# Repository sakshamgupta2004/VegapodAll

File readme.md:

1. This is the all the vegapod work from my side
2. MP4s are not uploaded for obvious reasons
3. some backup folders generated by kicad and other cache is added to gitignore aswell
4. If any folder appears empty when it should have content, its probably added to gitignore
5. Contains Videos, Images, PCB designs, Meeting info, Documents such as fdd and itd, SPICE simulations, etc

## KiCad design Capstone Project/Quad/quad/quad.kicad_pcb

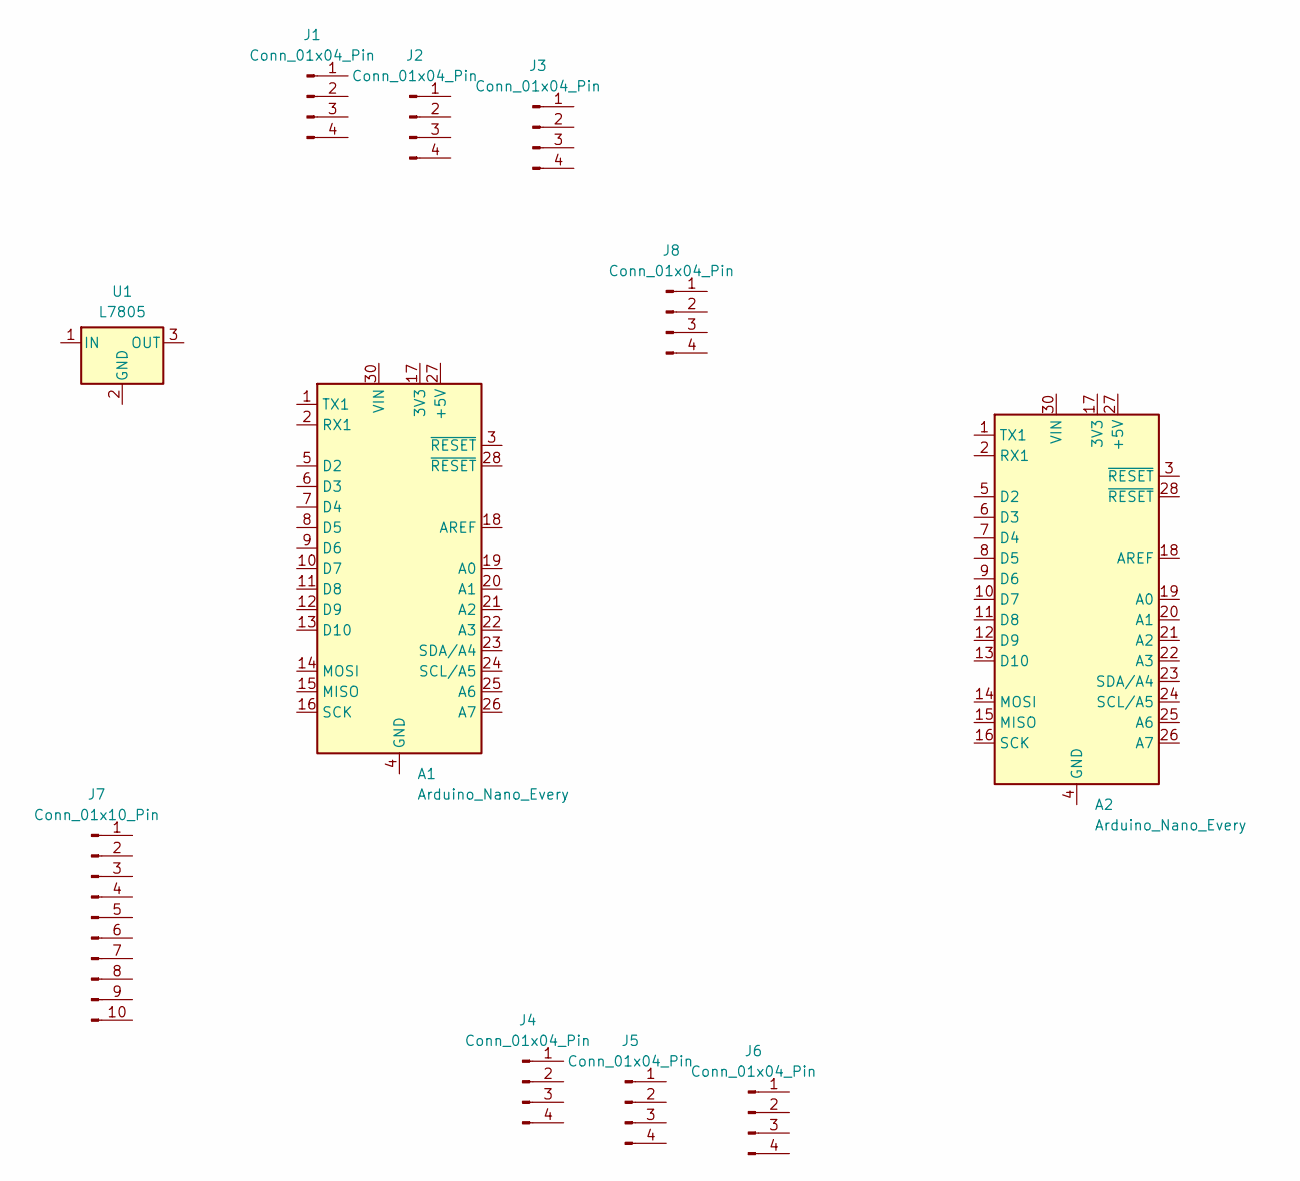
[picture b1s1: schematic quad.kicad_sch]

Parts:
A1, A2: Arduino_Nano_Every; Arduino_Nano
J1, J2, J3, J4, J5, J6, J8: Conn_01x04_Pin; PinHeader_1x04_P2.54mm_Vertical
J7: Conn_01x10_Pin; PinHeader_1x10_P2.54mm_Vertical
U1: L7805; TO-220-3_Vertical

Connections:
unnamed: A1.4 (GND), A1.29 (GND)
unnamed: A2.4 (GND), A2.29 (GND)

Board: 2 copper layers, 11 parts (0 on the bottom side), 2 nets, no tracks yet.

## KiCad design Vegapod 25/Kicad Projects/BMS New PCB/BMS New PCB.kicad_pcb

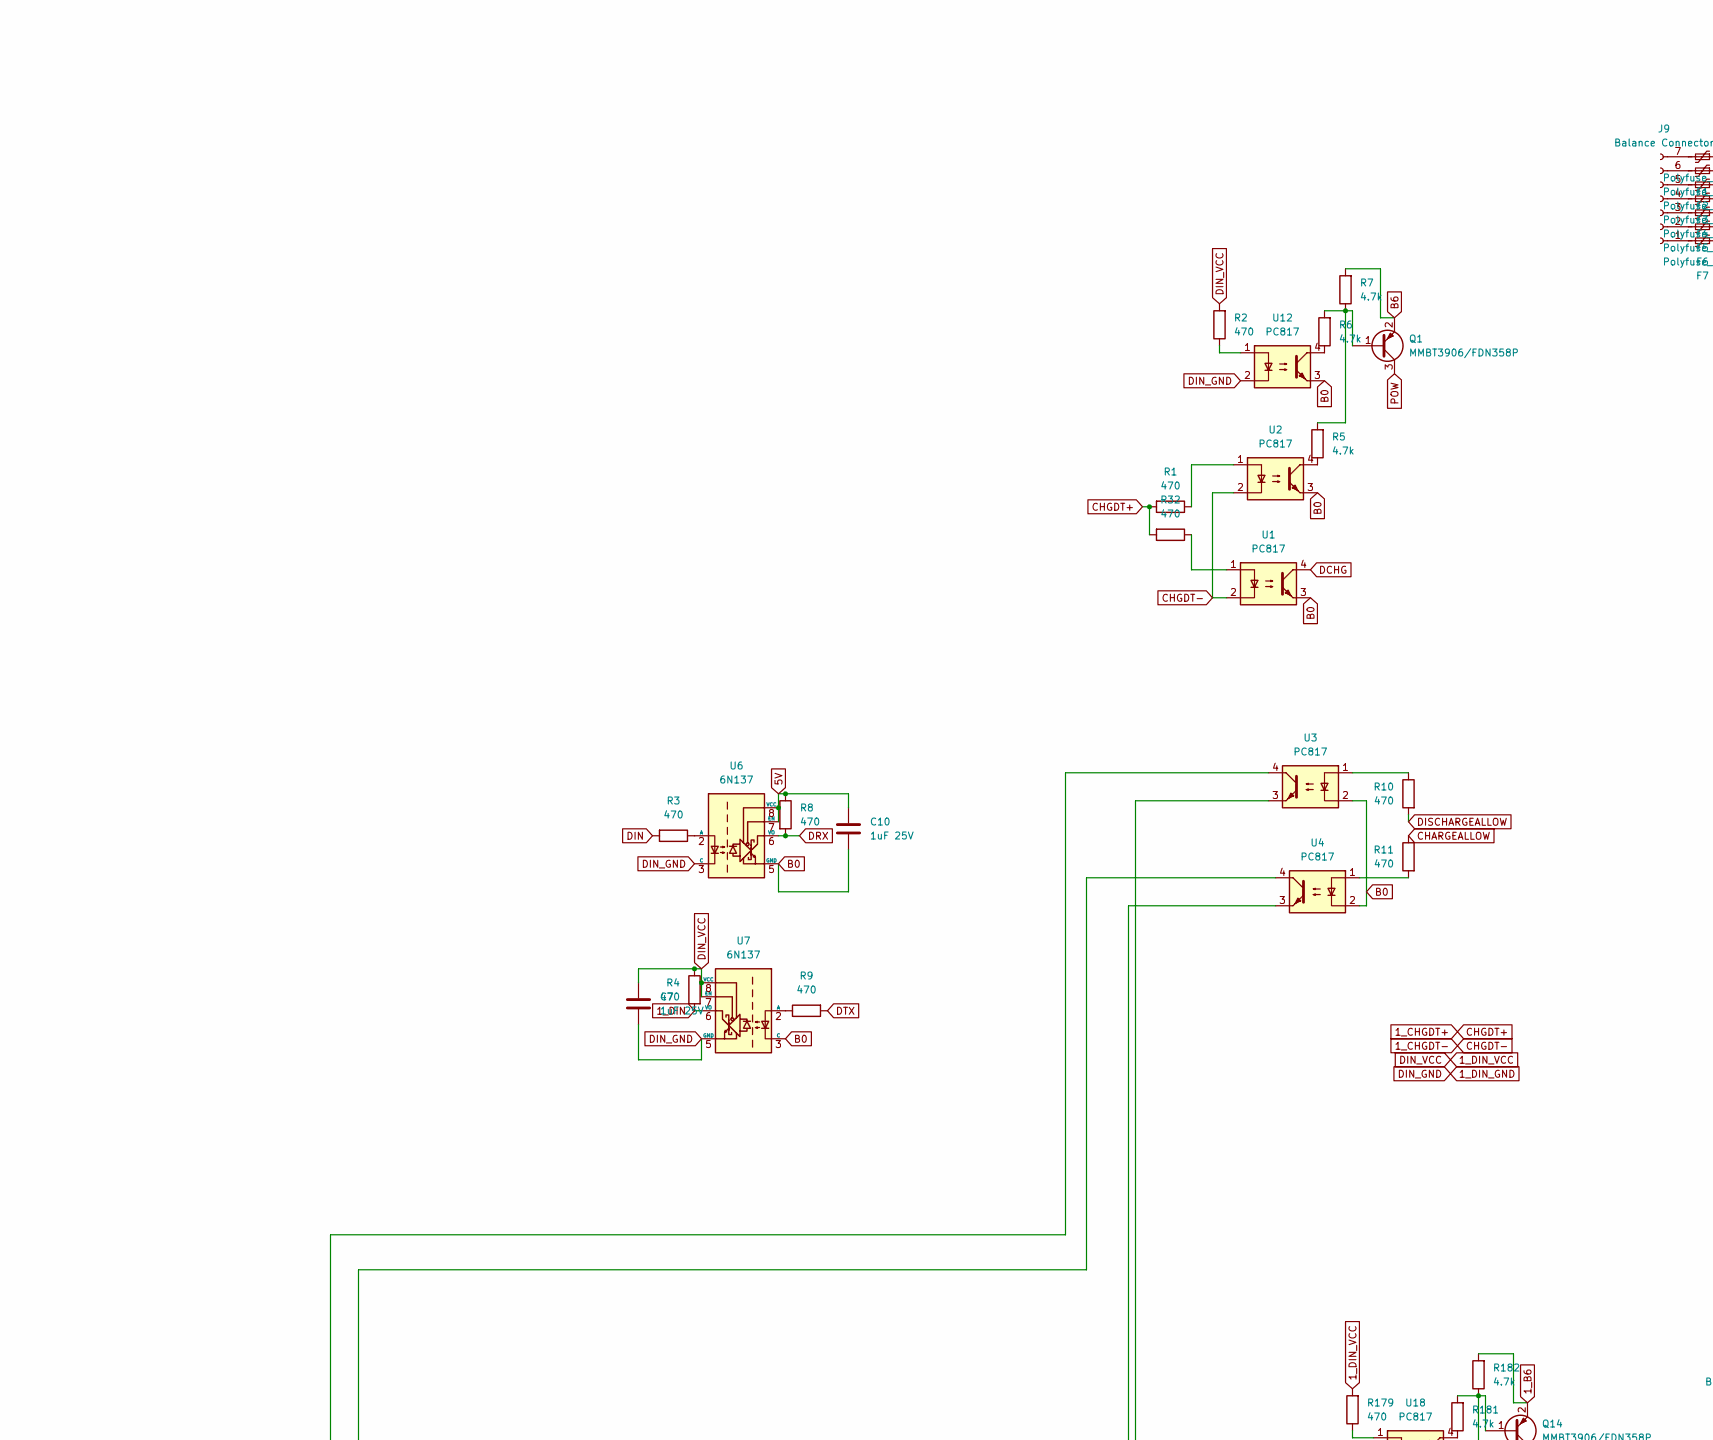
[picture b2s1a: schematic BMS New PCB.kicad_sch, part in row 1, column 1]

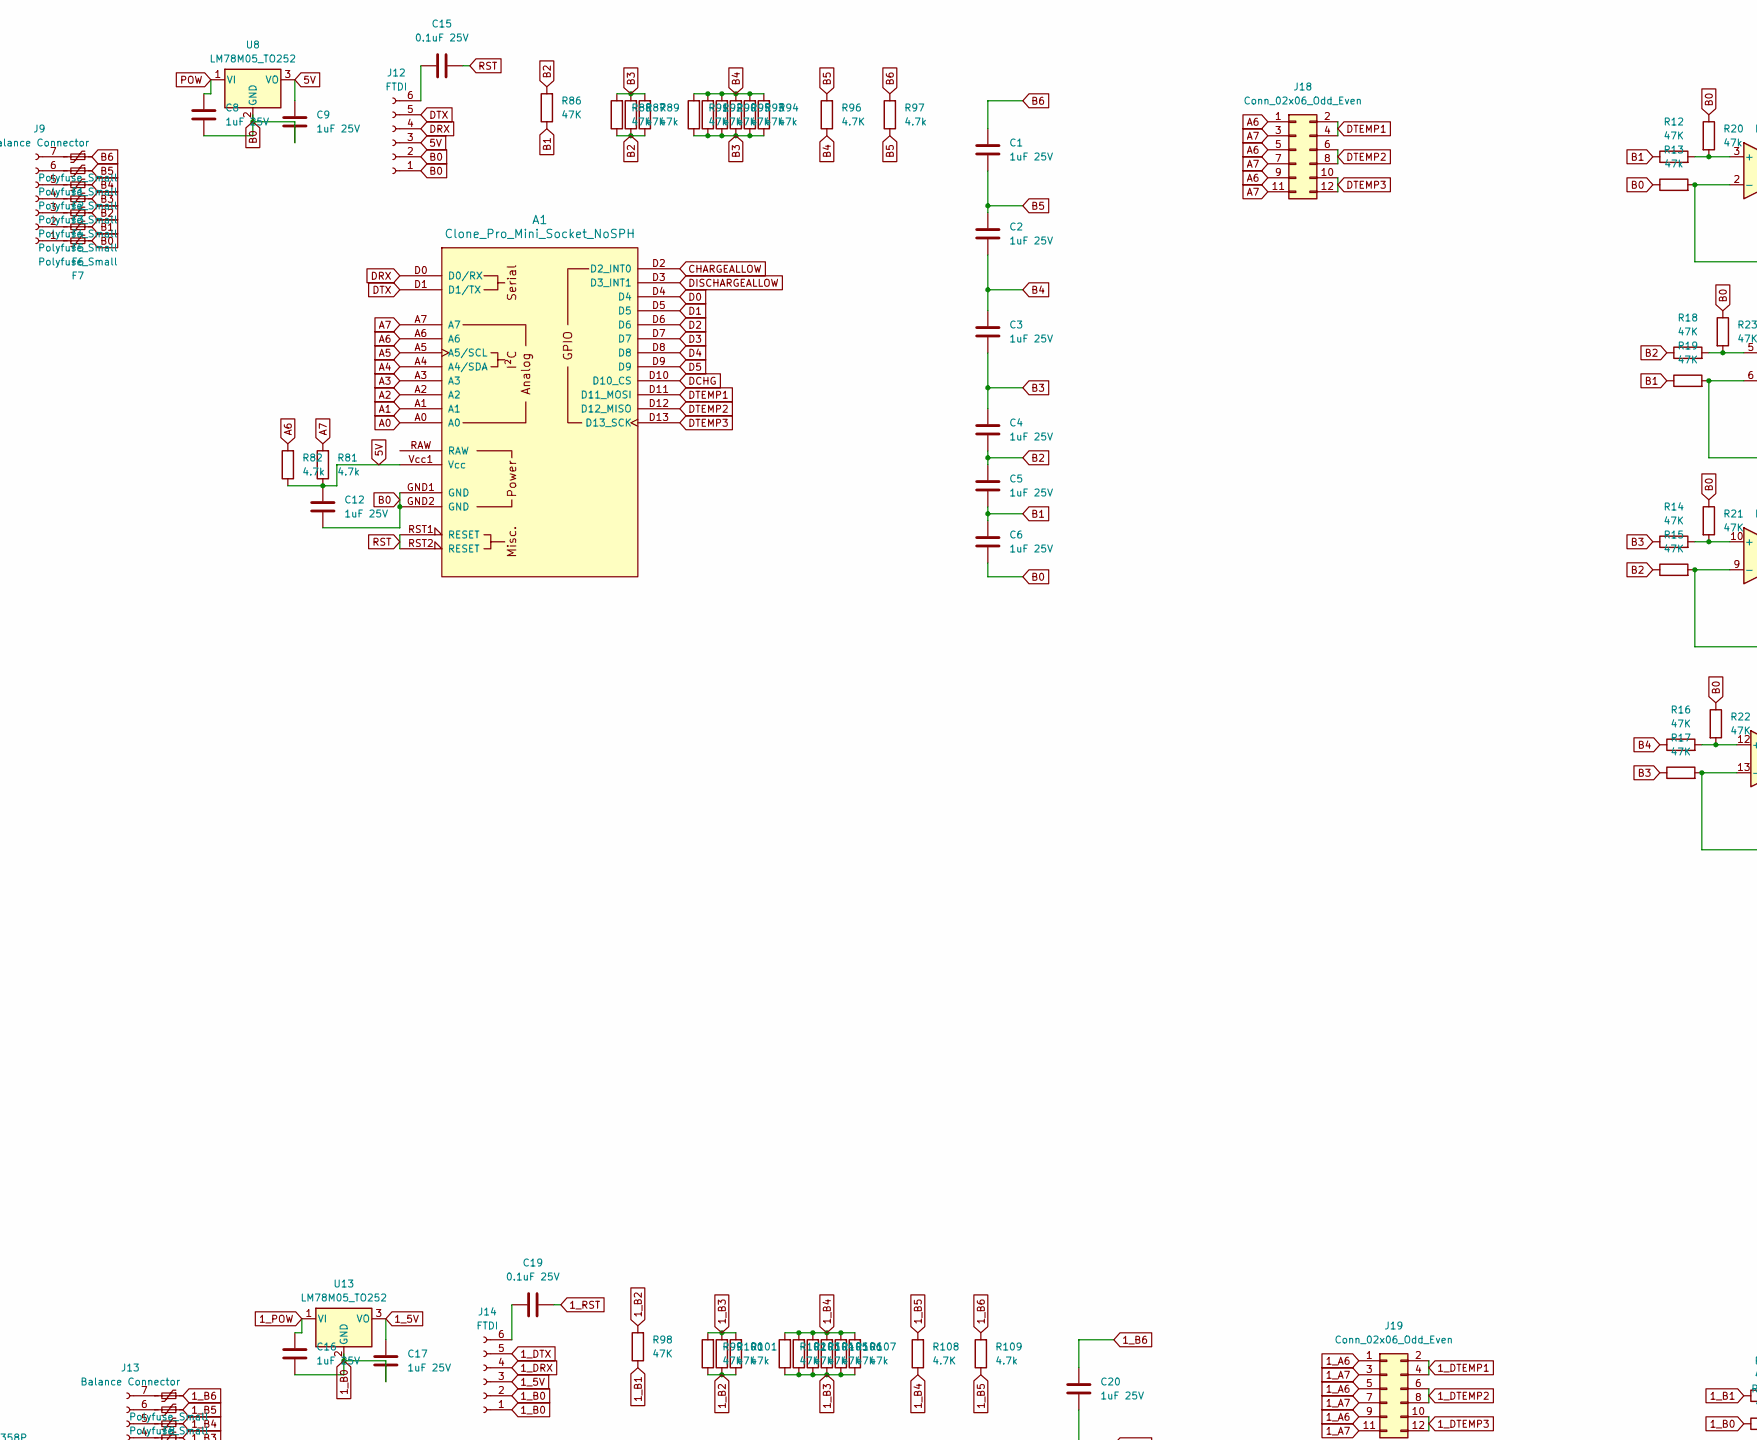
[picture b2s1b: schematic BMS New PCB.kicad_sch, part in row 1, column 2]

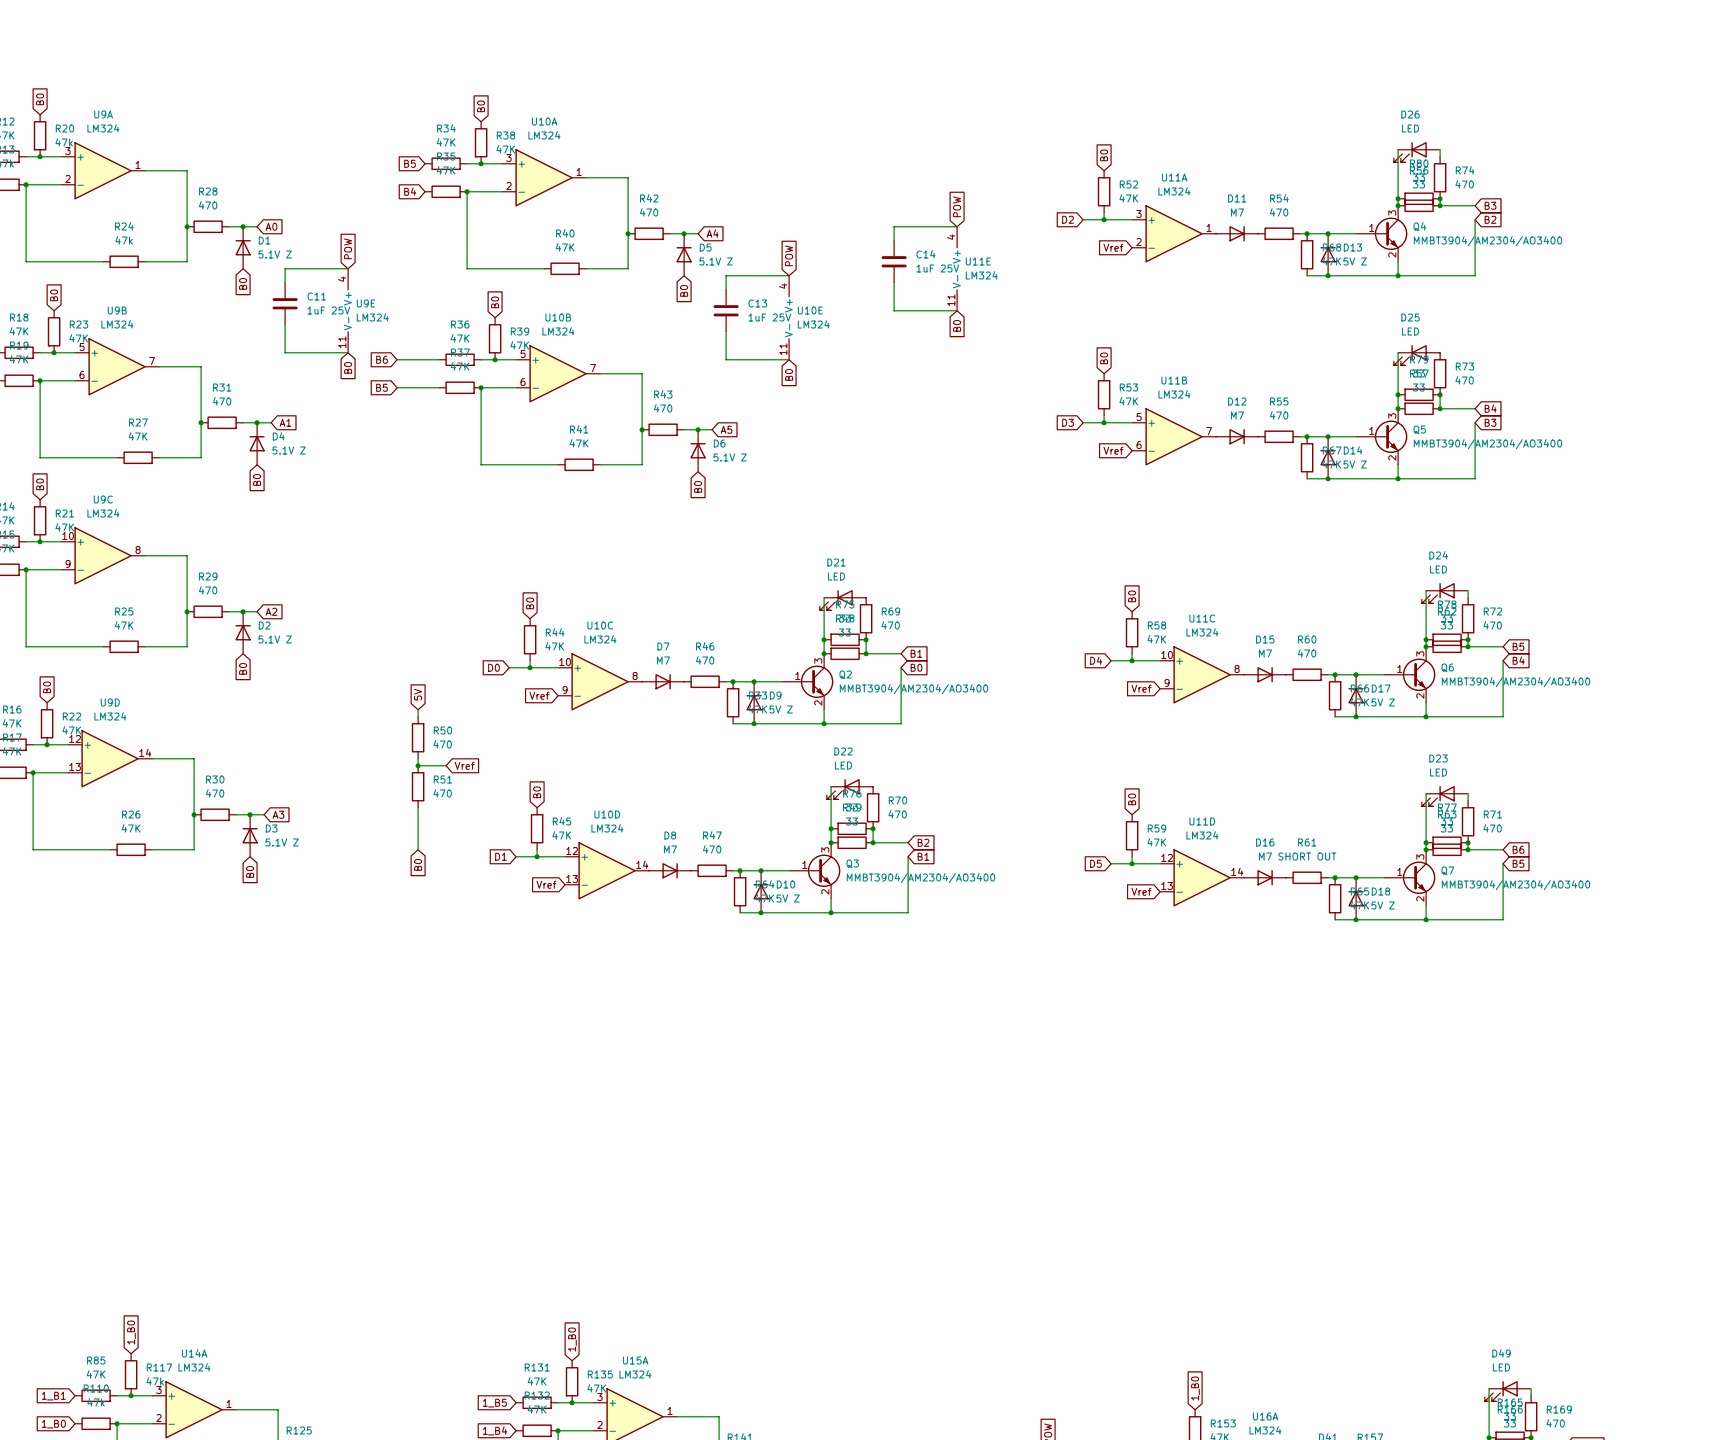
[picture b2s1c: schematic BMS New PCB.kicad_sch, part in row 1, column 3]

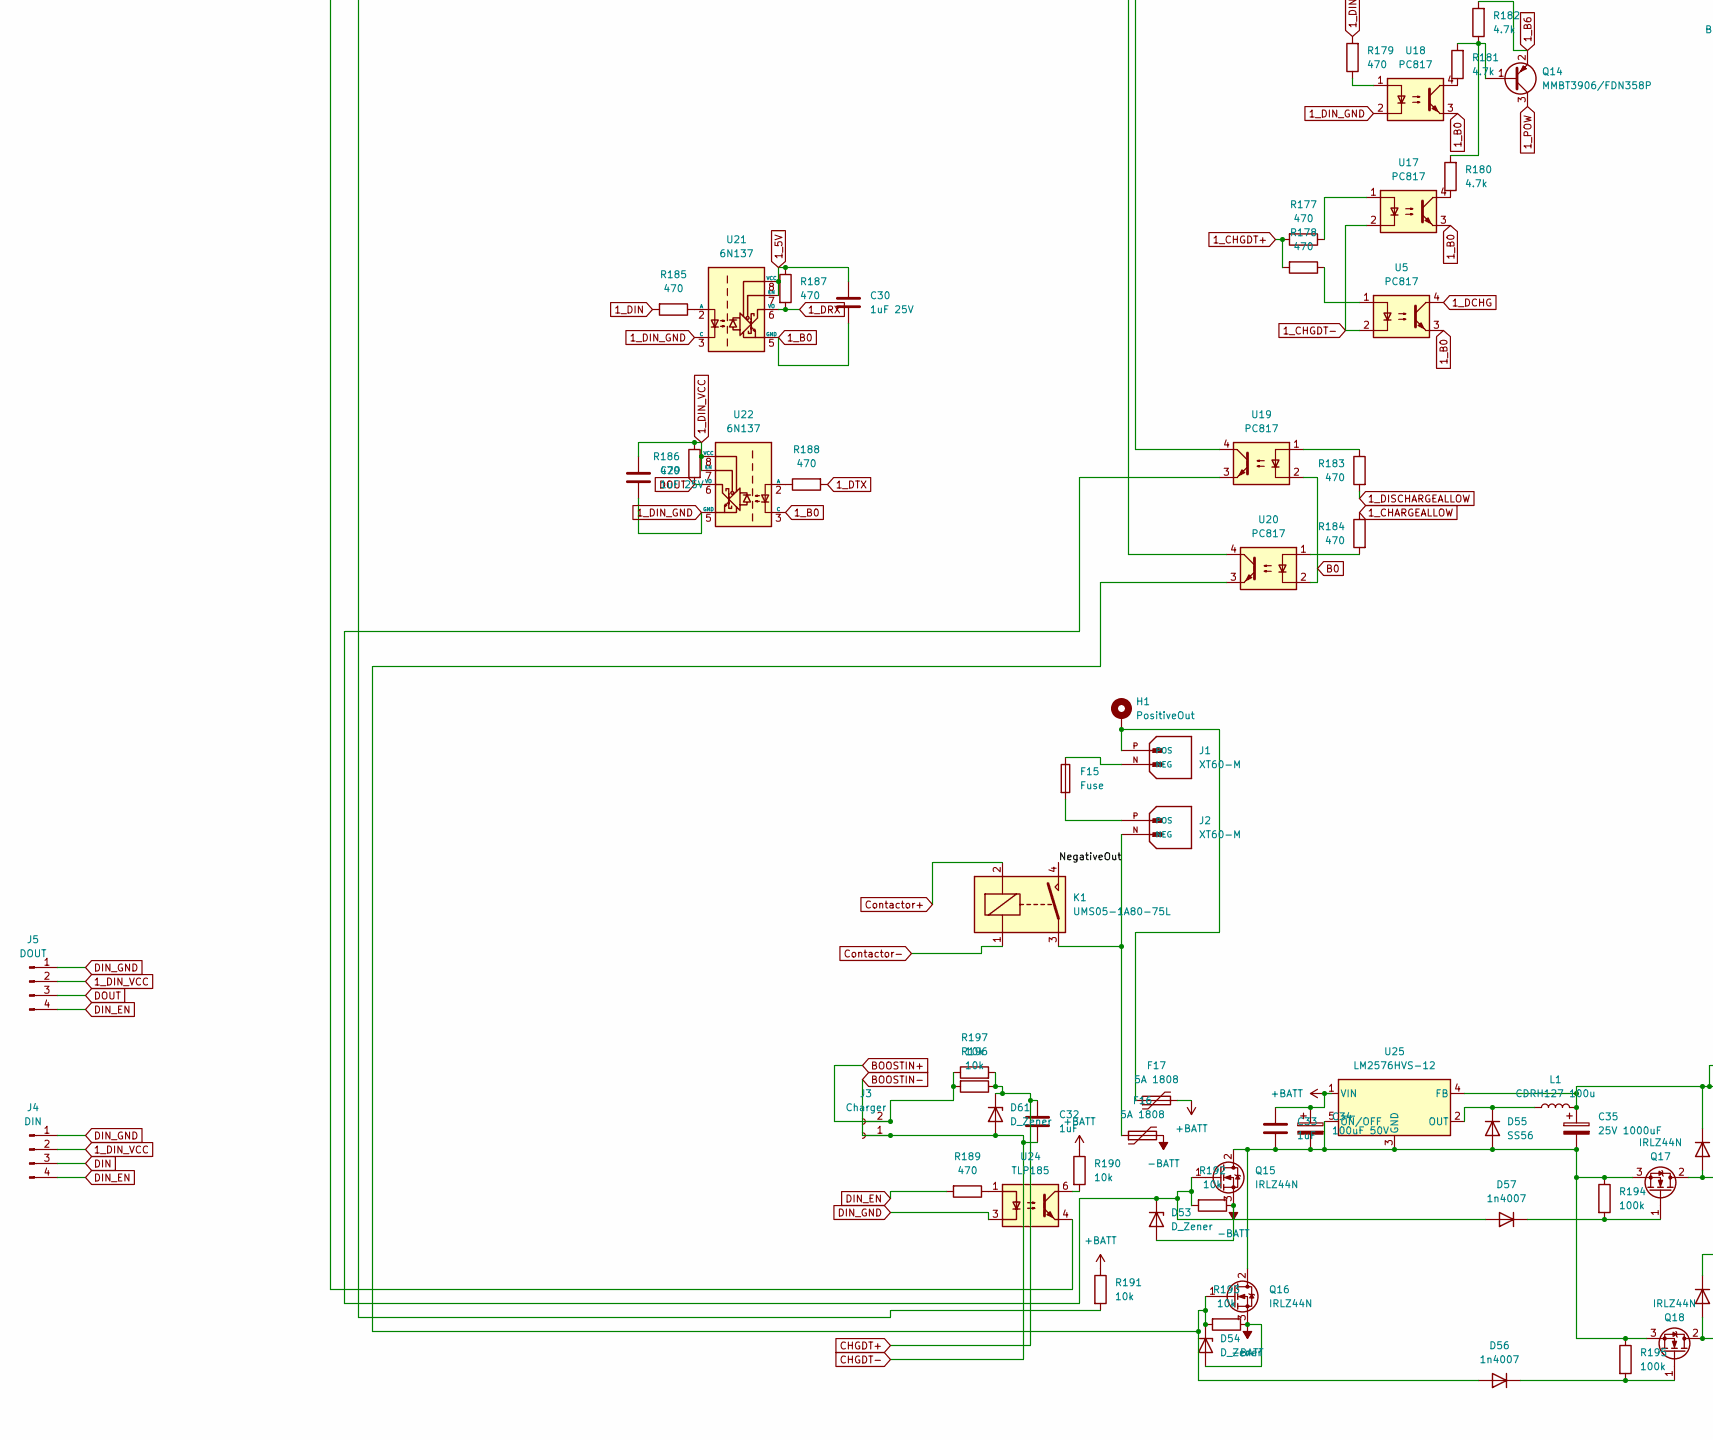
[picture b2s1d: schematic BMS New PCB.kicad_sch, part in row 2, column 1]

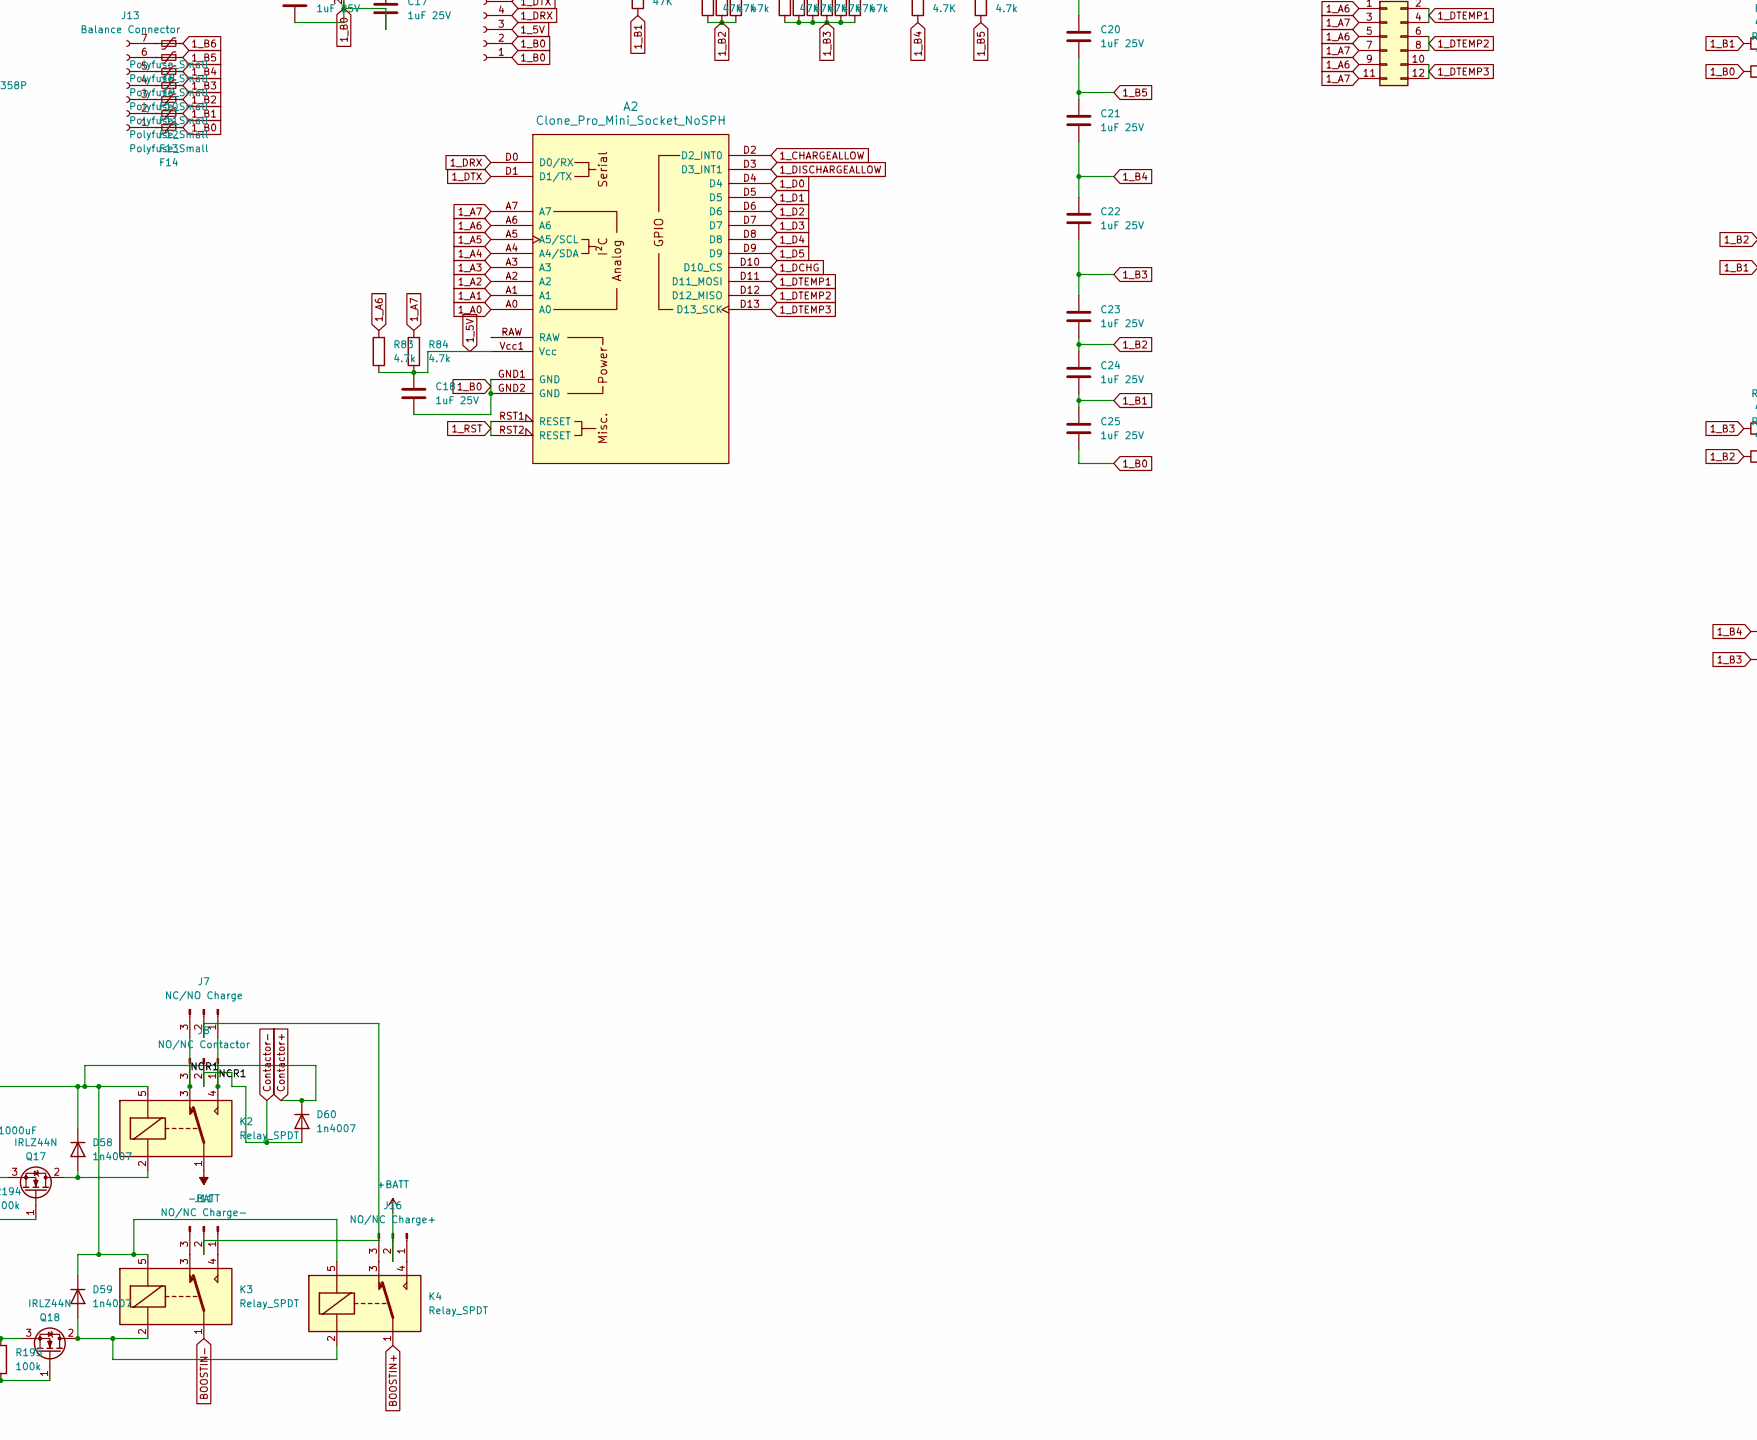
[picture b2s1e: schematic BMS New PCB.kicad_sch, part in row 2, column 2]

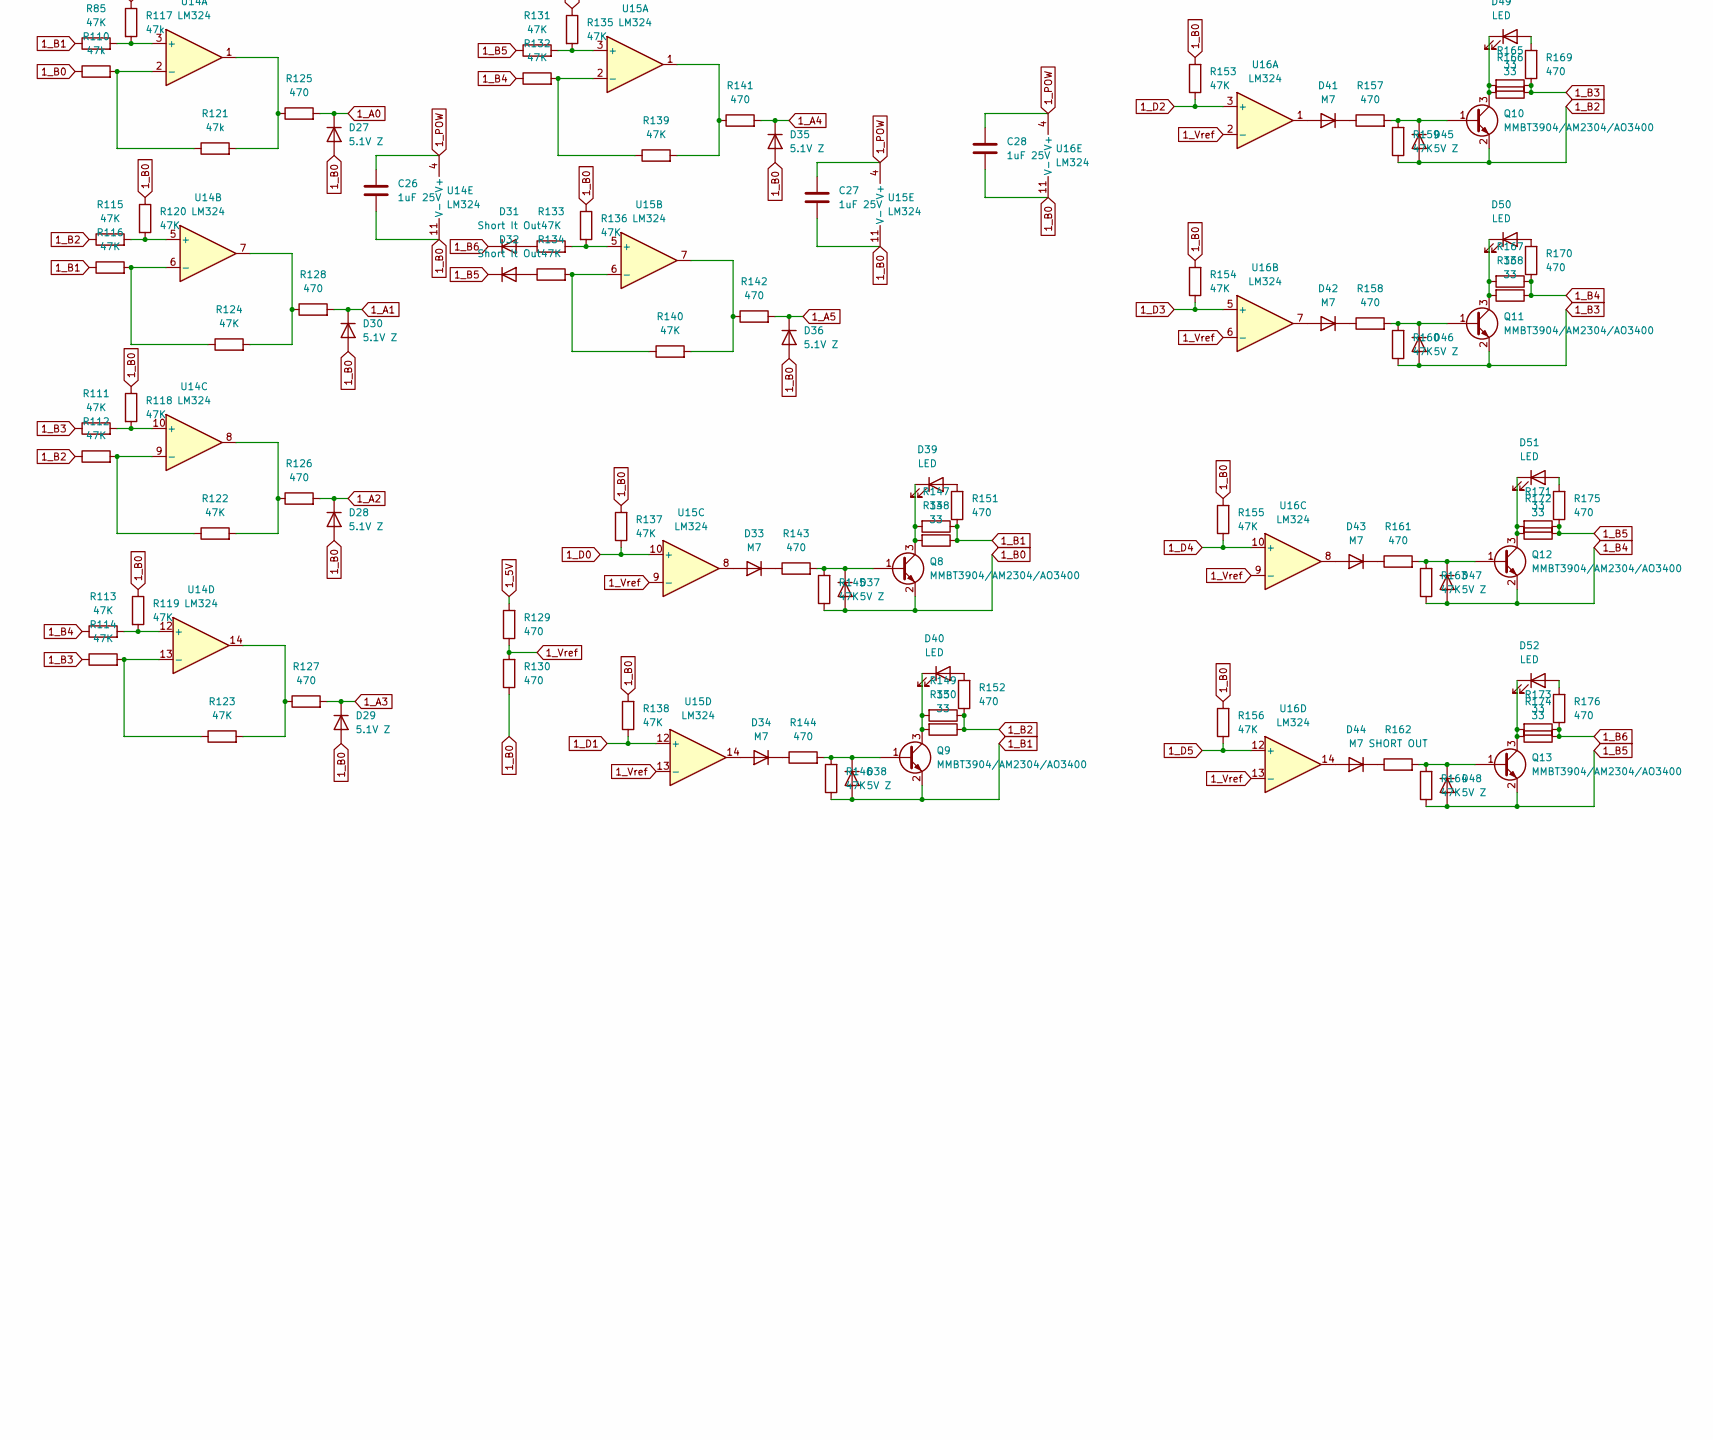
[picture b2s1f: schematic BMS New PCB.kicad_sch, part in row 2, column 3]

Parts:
A1, A2: Clone_Pro_Mini_Socket_NoSPH; Clone_Pro_Mini_Socket_NoSPH_Extraanalog
C1, C2, C3, C4, C5, C6, C7, C8, C9, C10, C11, C12, C13, C14, C16, C17, C18, C20, C21, C22, C23, C24, C25, C26, C27, C28, C29, C30: 1uF 25V; C_1206_3216Metric_Pad1.33x1.80mm_HandSolder
C15, C19: 0.1uF 25V; C_0805_2012Metric_Pad1.18x1.45mm_HandSolder
C32, C33: 1uF; C_1206_3216Metric_Pad1.33x1.80mm_HandSolder
C34: 100uF 50V; CP_Elec_8x10.5
C35: 25V 1000uF; CAP_EEEFK1E102AQ
D1, D2, D3, D4, D5, D6, D27, D28, D29, D30, D35, D36: 5.1V Z; D_SMA
D7, D8, D11, D12, D15, D16, D33, D34, D41, D42, D43, D44: M7; D_SMA
D9, D10, D13, D14, D17, D18, D37, D38, D45, D46, D47, D48: 5V Z; D_SMA
D21, D22, D23, D24, D25, D26, D39, D40, D49, D50, D51, D52: LED; D_0805_2012Metric_Pad1.15x1.40mm_HandSolder
D31, D32: Short It Out; D_SMA
D53, D54, D61: D_Zener; D_SMA_Handsoldering
D55: SS56; D_SMA-SMB_Universal_Handsoldering
D56, D57, D58, D59, D60: 1n4007; D_SMA
F1, F2, F3, F4, F5, F6, F7, F8, F9, F10, F11, F12, F13, F14: Polyfuse_Small; R_1206_3216Metric_Pad1.30x1.75mm_HandSolder
F15: Fuse; BLadeFuse
F16, F17: 5A 1808; R_1812_4532Metric_Pad1.30x3.40mm_HandSolder
H1: PositiveOut; MountingHole_8.4mm_M8_Pad
J1, J2: XT60-M; AMASS_XT60-M; PARTREV V1.2
J3: Charger; PhoenixContact_MCV_1,5_2-G-5.08_1x02_P5.08mm_Vertical
J4: DIN; JST_XH_B4B-XH-A_1x04_P2.50mm_Vertical
J5: DOUT; JST_XH_B4B-XH-A_1x04_P2.50mm_Vertical
J7: NC/NO Charge; PinHeader_1x03_P2.54mm_Vertical
J8: NO/NC Contactor; PinHeader_1x03_P2.54mm_Vertical
J9, J13: Balance Connector; PinSocket_1x07_P2.54mm_Vertical
J11: NO/NC Charge-; PinHeader_1x03_P2.54mm_Vertical
J12, J14: FTDI; PinSocket_1x06_P2.54mm_Horizontal
J16: NO/NC Charge+; PinHeader_1x03_P2.54mm_Vertical
J18, J19: Conn_02x06_Odd_Even; PinSocket_2x06_P2.00mm_Vertical
K1: UMS05-1A80-75L; HVC500B
K2, K3, K4: Relay_SPDT; Relay_SPDT_Omron-G5LE-1
L1: CDRH127 100u; L_12x12mm_H8mm
Q1, Q14: MMBT3906/FDN358P; SOT-23
Q2, Q3, Q4, Q5, Q6, Q7, Q8, Q9, Q10, Q11, Q12, Q13: MMBT3904/AM2304/AO3400; SOT-23
Q15, Q16, Q17, Q18: IRLZ44N; TO-220-3_Vertical
R1, R2, R3, R4, R8, R9, R10, R11, R28, R29, R30, R31, R32, R42, R43, R46, R47, R50, R51, R54, R55, R60, R69, R70, R71, R72, R73, R74, R125, R126, R127, R128, R129, R130, R141, R142, R143, R144, R151, R152, R157, R158, R161, R169, R170, R175, R176, R177, R178, R179, R183, R184, R185, R186, R187, R188, R189: 470; R_0805_2012Metric_Pad1.20x1.40mm_HandSolder
R5, R6, R7, R81, R82, R83, R84, R97, R109, R180, R181, R182: 4.7k; R_0805_2012Metric_Pad1.20x1.40mm_HandSolder
R12, R14, R15, R16, R17, R18, R19, R21, R22, R23, R25, R26, R27, R33, R34, R35, R36, R37, R38, R39, R40, R41, R44, R45, R52, R53, R58, R59, R64, R65, R66, R67, R68, R85, R86, R98, R111, R112, R113, R114, R115, R116, R118, R119, R120, R122, R123, R124, R131, R132, R133, R134, R135, R136, R137, R138, R139, R140, R145, R146, R153, R154, R155, R156, R159, R160, R163, R164: 47K; R_0805_2012Metric_Pad1.20x1.40mm_HandSolder
R13, R20, R24, R87, R88, R89, R90, R91, R92, R93, R94, R95, R99, R100, R101, R102, R103, R104, R105, R106, R107, R110, R117, R121: 47k; R_0805_2012Metric_Pad1.20x1.40mm_HandSolder
R48, R49, R56, R57, R62, R63, R75, R76, R77, R78, R79, R80, R147, R148, R149, R150, R165, R166, R167, R168, R171, R172, R173, R174: 33; R_1206_3216Metric_Pad1.30x1.75mm_HandSolder
R61, R162: SHORT OUT; R_0805_2012Metric_Pad1.20x1.40mm_HandSolder
R96, R108: 4.7K; R_0805_2012Metric_Pad1.20x1.40mm_HandSolder
R190, R191, R192, R193, R196, R197: 10k; R_0805_2012Metric_Pad1.20x1.40mm_HandSolder
R194, R195: 100k; R_0805_2012Metric_Pad1.20x1.40mm_HandSolder
U1, U2, U3, U4, U5, U12, U17, U18, U19, U20: PC817; SSO-4_6.7x5.1mm_P2.54mm_Clearance8mm
U6, U7, U21, U22: 6N137; SSO-8_6.7x9.8mm_P2.54mm_Clearance8mm
U8, U13: LM78M05_TO252; TO-252-2
U9, U10, U11, U14, U15, U16: LM324; SOIC-14_3.9x8.7mm_P1.27mm
U24: TLP185; SOIC-4_4.55x3.7mm_P2.54mm
U25: LM2576HVS-12; TO-263-5_TabPin3

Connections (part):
1_5V: A2.Vcc1 (Vcc), C17.1, C18.1, C30.1, J14.3, R83.1, R84.1, R129.2, R187.1, U13.3 (VO), U21.7 (EN), U21.8 (VCC)
1_A0: A2.A0, D27.1 (K), R125.2
1_A1: A2.A1, D30.1 (K), R128.2
1_A2: A2.A2, D28.1 (K), R126.2
1_A3: A2.A3, D29.1 (K), R127.2
1_A4: A2.A4 (A4/SDA), D35.1 (K), R141.2
1_A5: A2.A5 (A5/SCL), D36.1 (K), R142.2
1_A6: A2.A6, J19.1, J19.5, J19.9, R83.2
1_A7: A2.A7, J19.3, J19.7, J19.11, R84.2
1_B0: A2.GND1 (GND), A2.GND2 (GND), C16.2, C17.2, C18.2, C25.1, C26.2, C27.2, C28.2, C30.2, D27.2 (A), D28.2 (A), D29.2 (A), D30.2 (A), D35.2 (A), D36.2 (A), D37.2 (A), F14.1, J14.1, J14.2, Q8.2 (E), R110.1, R117.1, R118.1, R119.1, R120.1, R130.1, R135.1, R136.1, R137.2, R138.2, R145.1, R153.2, R154.2, R155.2, R156.2, U5.3, U13.2 (GND), U14.11 (V-), U15.11 (V-), U16.11 (V-), U17.3, U18.3, U21.5 (GND), U22.3 (C)
1_B1: C24.1, C25.2, D38.2 (A), F13.1, Q9.2 (E), R85.1, R98.1, R116.1, R146.1, R147.1, R148.1, R151.1
1_B2: C23.1, C24.2, D45.2 (A), F12.1, Q10.2 (E), R98.2, R99.1, R100.1, R101.1, R112.1, R115.1, R149.1, R150.1, R152.1, R159.1
1_B3: C22.1, C23.2, D46.2 (A), F11.1, Q11.2 (E), R99.2, R100.2, R101.2, R102.1, R103.1, R104.1, R105.1, R106.1, R107.1, R111.1, R114.1, R160.1, R165.1, R166.1, R169.1
1_B4: C21.1, C22.2, D47.2 (A), F10.1, Q12.2 (E), R102.2, R103.2, R104.2, R105.2, R106.2, R107.2, R108.1, R113.1, R132.1, R163.1, R167.1, R168.1, R170.1
1_B5: C20.1, C21.2, D32.1 (K), D48.2 (A), F9.1, Q13.2 (E), R108.2, R109.1, R131.1, R164.1, R171.1, R172.1, R175.1
1_B6: C20.2, D31.1 (K), F8.1, Q14.2 (E), R109.2, R173.1, R174.1, R176.1, R182.2
1_CHARGEALLOW: A2.D2 (D2_INT0), R184.1
1_CHGDT+: C32.1, D61.1 (K), R1.2, R32.2, R177.2, R178.2, R196.1, R197.2
1_CHGDT-: C32.2, D61.2 (A), J3.1, K3.1, U1.2, U2.2, U5.2, U17.2
1_D0: A2.D4, R137.1, U15.10 (+)
1_D1: A2.D5, R138.1, U15.12 (+)
1_D2: A2.D6, R153.1, U16.3 (+)
1_D3: A2.D7, R154.1, U16.5 (+)
1_D4: A2.D8, R155.1, U16.10 (+)
1_D5: A2.D9, R156.1, U16.12 (+)
1_DCHG: A2.D10 (D10_CS), U5.4
1_DIN: R4.2, R185.2, U7.6 (VO)
1_DIN_GND: C7.2, C29.2, J4.1, J5.1, U6.3 (C), U7.5 (GND), U12.2, U18.2, U21.3 (C), U22.5 (GND), U24.3
1_DIN_VCC: C7.1, C29.1, J4.2, J5.2, R2.2, R4.1, R179.2, R186.1, U7.7 (EN), U7.8 (VCC), U22.7 (EN), U22.8 (VCC)
1_DISCHARGEALLOW: A2.D3 (D3_INT1), R183.2
1_DRX: A2.D0 (D0/RX), J14.4, R187.2, U21.6 (VO)
1_DTEMP1: A2.D11 (D11_MOSI), J19.2, J19.4
1_DTEMP2: A2.D12 (D12_MISO), J19.6, J19.8
1_DTEMP3: A2.D13 (D13_SCK), J19.10, J19.12
1_DTX: A2.D1 (D1/TX), J14.5, R188.2
1_POW: C16.1, C26.1, C27.1, C28.1, Q14.3 (C), U13.1 (VI), U14.4 (V+), U15.4 (V+), U16.4 (V+)
1_RST: A2.RST1 (RESET), A2.RST2 (RESET), C19.2
1_Vref: R129.1, R130.2, U15.9 (-), U15.13 (-), U16.2 (-), U16.6 (-), U16.9 (-), U16.13 (-)
5V: A1.Vcc1 (Vcc), C9.1, C10.1, C12.1, J12.3, R8.1, R50.2, R81.1, R82.1, U6.7 (EN), U6.8 (VCC), U8.3 (VO)
+BATT: C33.1, C34.1, F17.2, J16.2, R190.1, R191.1, U25.1 (VIN)
-BATT: D53.2 (A), D54.2 (A), F16.2, K2.1, Q15.3 (S), Q16.3 (S), R192.1, R193.1
/NCR1: J7.1, J8.1, K2.4
/NOR1: J7.3, J8.3, K2.3
/NegativeOut: K1.4
A0: A1.A0, D1.1 (K), R28.2
A1: A1.A1, D4.1 (K), R31.2
A2: A1.A2, D2.1 (K), R29.2
A3: A1.A3, D3.1 (K), R30.2
A4: A1.A4 (A4/SDA), D5.1 (K), R42.2
A5: A1.A5 (A5/SCL), D6.1 (K), R43.2
A6: A1.A6, J18.1, J18.5, J18.9, R82.2
A7: A1.A7, J18.3, J18.7, J18.11, R81.2
B0: A1.GND1 (GND), A1.GND2 (GND), C6.1, C8.2, C9.2, C10.2, C11.2, C12.2, C13.2, C14.2, D1.2 (A), D2.2 (A), D3.2 (A), D4.2 (A), D5.2 (A), D6.2 (A), D9.2 (A), F7.1, J12.1, J12.2, Q2.2 (E), R13.1, R20.1, R21.1, R22.1, R23.1, R33.1, R38.1, R39.1, R44.2, R45.2, R51.1, R52.2, R53.2, R58.2, R59.2, U1.3, U2.3, U3.2, U4.2, U6.5 (GND), U7.3 (C), U8.2 (GND), U9.11 (V-), U10.11 (V-), U11.11 (V-), U12.3, U19.2, U20.2
B1: C5.1, C6.2, D10.2 (A), F6.1, Q3.2 (E), R12.1, R19.1, R48.1, R64.1, R69.1, R75.1, R86.1
B2: C4.1, C5.2, D13.2 (A), F5.1, Q4.2 (E), R15.1, R18.1, R49.1, R68.1, R70.1, R76.1, R86.2, R87.1, R88.1, R89.1
B3: C3.1, C4.2, D14.2 (A), F4.1, Q5.2 (E), R14.1, R17.1, R56.1, R67.1, R74.1, R80.1, R87.2, R88.2, R89.2, R90.1, R91.1, R92.1, R93.1, R94.1, R95.1
B4: C2.1, C3.2, D17.2 (A), F3.1, Q6.2 (E), R16.1, R35.1, R57.1, R66.1, R73.1, R79.1, R90.2, R91.2, R92.2, R93.2, R94.2, R95.2, R96.1
B5: C1.1, C2.2, D18.2 (A), F2.1, Q7.2 (E), R34.1, R37.1, R62.1, R65.1, R72.1, R78.1, R96.2, R97.1
B6: C1.2, F1.1, Q1.2 (E), R7.2, R36.1, R63.1, R71.1, R77.1, R97.2
BOOSTIN+: J3.2, K4.1, R196.2, R197.1
CHARGEALLOW: A1.D2 (D2_INT0), R11.1
Contactor+: C35.1, D58.1 (K), D59.1 (K), D60.1 (K), K1.2, K2.5, K3.5, K4.5, L1.2, U25.4 (FB)
Contactor-: D60.2 (A), J8.2, K1.1
D0: A1.D4, R44.1, U10.10 (+)
D1: A1.D5, R45.1, U10.12 (+)
D2: A1.D6, R52.1, U11.3 (+)
D3: A1.D7, R53.1, U11.5 (+)
D4: A1.D8, R58.1, U11.10 (+)
D5: A1.D9, R59.1, U11.12 (+)
DCHG: A1.D10 (D10_CS), U1.4
DIN: J4.3, R3.2
DIN_EN: J4.4, J5.4, R189.2
DISCHARGEALLOW: A1.D3 (D3_INT1), R10.2
DOUT: J5.3, R186.2, U22.6 (VO)
DRX: A1.D0 (D0/RX), J12.4, R8.2, U6.6 (VO)
DTEMP1: A1.D11 (D11_MOSI), J18.2, J18.4
DTEMP2: A1.D12 (D12_MISO), J18.6, J18.8
DTEMP3: A1.D13 (D13_SCK), J18.10, J18.12
DTX: A1.D1 (D1/TX), J12.5, R9.2
unnamed: D7.2 (A), U10.8
unnamed: D7.1 (K), R46.1
unnamed: D8.2 (A), U10.14
unnamed: D8.1 (K), R47.1
unnamed: D9.1 (K), Q2.1 (B), R33.2, R46.2
unnamed: D10.1 (K), Q3.1 (B), R47.2, R64.2
unnamed: D11.2 (A), U11.1
unnamed: D11.1 (K), R54.1
unnamed: D12.2 (A), U11.7
unnamed: D12.1 (K), R55.1
unnamed: D13.1 (K), Q4.1 (B), R54.2, R68.2
unnamed: D14.1 (K), Q5.1 (B), R55.2, R67.2
unnamed: D15.2 (A), U11.8
unnamed: D15.1 (K), R60.1
unnamed: D16.2 (A), U11.14
unnamed: D16.1 (K), R61.1
unnamed: D17.1 (K), Q6.1 (B), R60.2, R66.2
unnamed: D18.1 (K), Q7.1 (B), R61.2, R65.2
unnamed: D21.2 (A), R69.2
unnamed: D21.1 (K), Q2.3 (C), R48.2, R75.2
unnamed: D22.2 (A), R70.2
unnamed: D22.1 (K), Q3.3 (C), R49.2, R76.2
unnamed: D23.2 (A), R71.2
unnamed: D23.1 (K), Q7.3 (C), R63.2, R77.2
unnamed: D24.2 (A), R72.2
unnamed: D24.1 (K), Q6.3 (C), R62.2, R78.2
unnamed: D25.2 (A), R73.2
unnamed: D25.1 (K), Q5.3 (C), R57.2, R79.2
unnamed: D26.2 (A), R74.2
unnamed: D26.1 (K), Q4.3 (C), R56.2, R80.2
unnamed: D31.2 (A), R133.1
unnamed: D32.2 (A), R134.1
unnamed: D33.2 (A), U15.8
unnamed: D33.1 (K), R143.1
unnamed: D34.2 (A), U15.14
unnamed: D34.1 (K), R144.1
unnamed: D37.1 (K), Q8.1 (B), R143.2, R145.2
unnamed: D38.1 (K), Q9.1 (B), R144.2, R146.2
unnamed: D39.2 (A), R151.2
unnamed: D39.1 (K), Q8.3 (C), R147.2, R148.2
unnamed: D40.2 (A), R152.2
unnamed: D40.1 (K), Q9.3 (C), R149.2, R150.2
unnamed: D41.2 (A), U16.1
unnamed: D41.1 (K), R157.1
unnamed: D42.2 (A), U16.7
unnamed: D42.1 (K), R158.1
unnamed: D43.2 (A), U16.8
unnamed: D43.1 (K), R161.1
unnamed: D44.2 (A), U16.14
unnamed: D44.1 (K), R162.1
unnamed: D45.1 (K), Q10.1 (B), R157.2, R159.2
unnamed: D46.1 (K), Q11.1 (B), R158.2, R160.2
unnamed: D47.1 (K), Q12.1 (B), R161.2, R163.2
unnamed: D48.1 (K), Q13.1 (B), R162.2, R164.2
unnamed: D49.2 (A), R169.2
unnamed: D49.1 (K), Q10.3 (C), R165.2, R166.2
unnamed: D50.2 (A), R170.2
unnamed: D50.1 (K), Q11.3 (C), R167.2, R168.2
unnamed: D51.2 (A), R175.2
unnamed: D51.1 (K), Q12.3 (C), R171.2, R172.2
unnamed: D52.2 (A), R176.2
unnamed: D52.1 (K), Q13.3 (C), R173.2, R174.2
unnamed: D53.1 (K), D57.2 (A), Q15.1 (G), R192.2, U19.3
unnamed: D54.1 (K), D56.2 (A), Q16.1 (G), R193.2, U20.3
unnamed: C33.2, C34.2, C35.2, D55.2 (A), Q15.2 (D), Q16.2 (D), Q17.3 (S), Q18.3 (S), R194.1, R195.1, U25.3 (GND), U25.5 (~ON/OFF)
unnamed: D55.1 (K), L1.1, U25.2 (OUT)
unnamed: D56.1 (K), Q18.1 (G), R195.2
unnamed: D57.1 (K), Q17.1 (G), R194.2
unnamed: D58.2 (A), K2.2, Q17.2 (D)
unnamed: D59.2 (A), K3.2, K4.2, Q18.2 (D)
unnamed: F15.1, J1.N (NEG)
unnamed: F17.1, H1.1, J1.P (POS)
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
